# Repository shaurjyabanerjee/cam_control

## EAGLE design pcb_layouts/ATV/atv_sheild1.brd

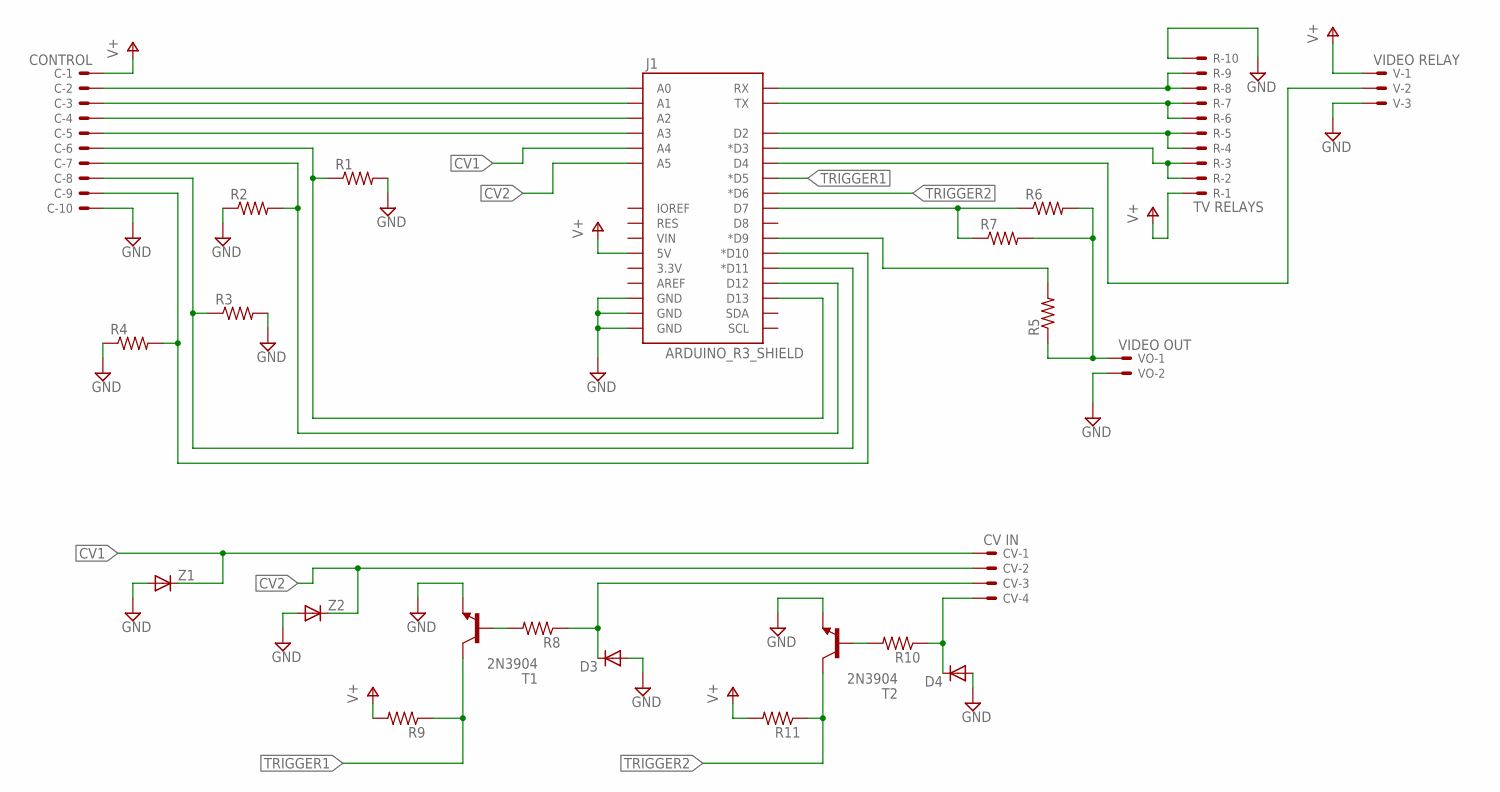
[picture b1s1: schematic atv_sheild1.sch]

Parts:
C: CONTROL; 22-23-2101
CV: CV IN; 22-23-2041
D3, D4: SMALL_DIODEDO35-7; DO35-7
J1: ARDUINO_R3_SHIELD; UNO_R3_SHIELD
R: TV RELAYS; 22-23-2101
R1, R2, R3, R4, R5, R6, R7, R8, R9, R10, R11: RESISTORPTH-1/4W; AXIAL-0.4
T1, T2: 2N3904; TO92
V: VIDEO RELAY; 22-23-2031
VO: VIDEO OUT; 22-23-2021
Z1, Z2: SMALL_DIODEDO35-7; DO35-7

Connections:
CV1: CV.1, J1.A4, Z1.C
CV2: CV.2, J1.A5, Z2.C
GND: C.10, D3.A, D4.A, J1.GND@0 (GND), J1.GND@1 (GND), J1.GND@2 (GND), R.10, R1.P$2 (2), R2.P$1 (1), R3.P$2 (2), R4.P$1 (1), T1.3 (E), T2.3 (E), V.3, VO.2, Z1.A, Z2.A
unnamed: J1.TX, R.6, R.7
unnamed: J1.D2, R.4, R.5
unnamed: J1.D3 (*D3), R.2, R.3
unnamed: J1.D4, V.2
unnamed: C.5, J1.A3
unnamed: C.2, J1.A0
unnamed: C.3, J1.A1
unnamed: C.4, J1.A2
unnamed: C.6, J1.D13, R1.P$1 (1)
unnamed: C.7, J1.D12, R2.P$2 (2)
unnamed: C.8, J1.D11 (*D11), R3.P$1 (1)
unnamed: C.9, J1.D10 (*D10), R4.P$2 (2)
unnamed: CV.3, D3.C, R8.P$1 (1)
unnamed: R5.P$1 (1), R6.P$2 (2), R7.P$2 (2), VO.1
unnamed: J1.D7, R6.P$1 (1), R7.P$1 (1)
unnamed: J1.D9 (*D9), R5.P$2 (2)
unnamed: R8.P$2 (2), T1.2 (B)
unnamed: CV.4, D4.C, R10.P$1 (1)
unnamed: J1.RX, R.8, R.9
unnamed: R10.P$2 (2), T2.2 (B)
TRIGGER1: J1.D5 (*D5), R9.P$1 (1), T1.1 (C)
TRIGGER2: J1.D6 (*D6), R11.P$1 (1), T2.1 (C)
V+: C.1, J1.5V, R.1, R9.P$2 (2), R11.P$2 (2), V.1

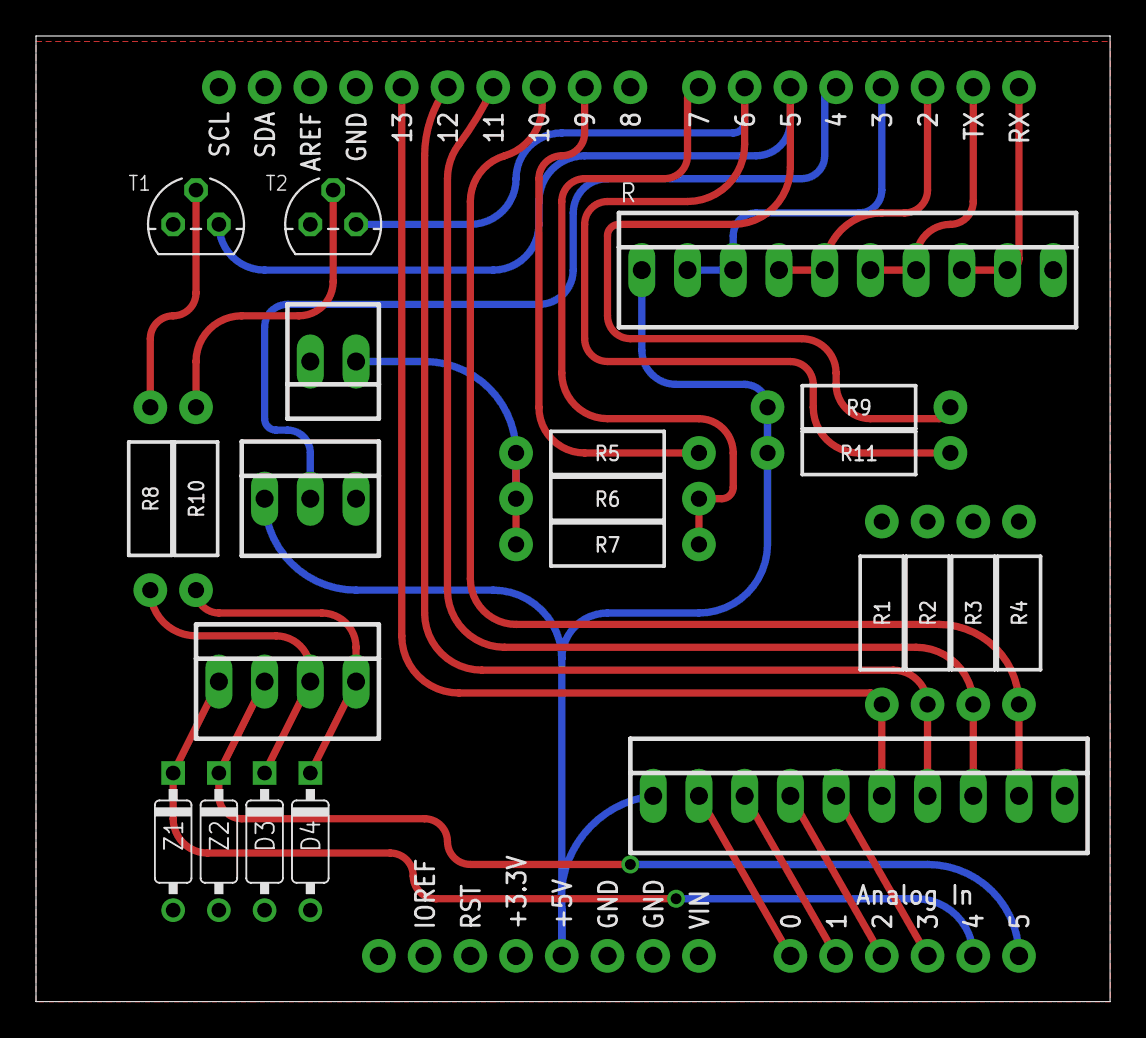
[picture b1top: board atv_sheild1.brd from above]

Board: 2 copper layers, 59.7 x 53.6 mm, 23 parts (0 on the bottom side), 26 nets.

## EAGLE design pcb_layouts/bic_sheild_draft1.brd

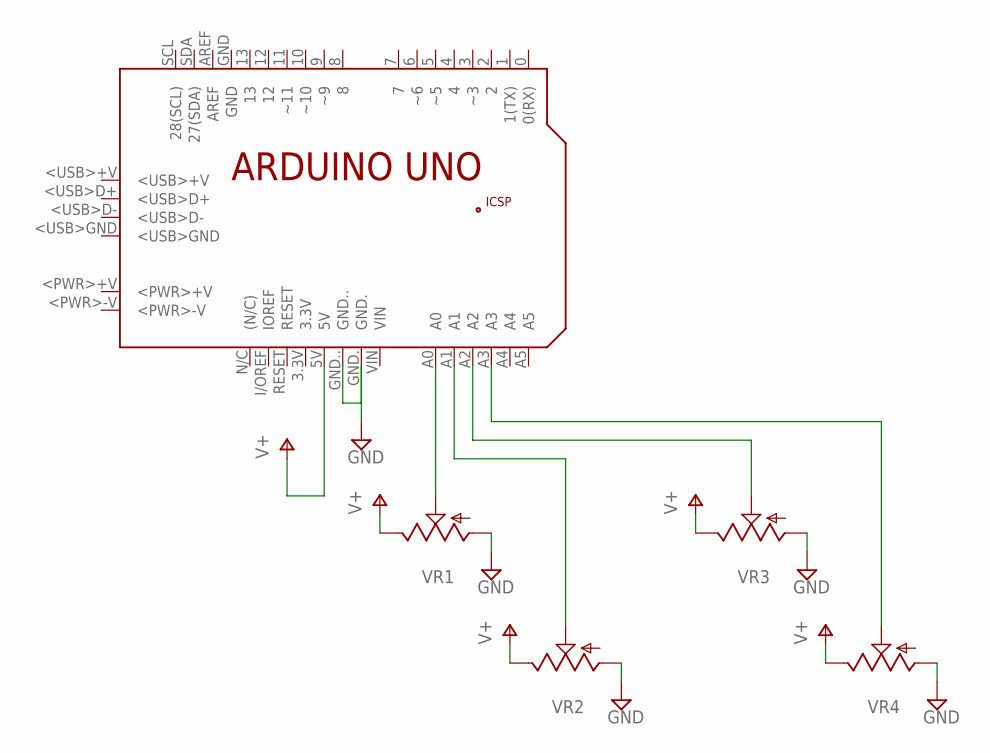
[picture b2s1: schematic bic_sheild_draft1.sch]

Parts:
PCB1: ARDUINO_UNO
VR1, VR2, VR3, VR4: 9MM_SNAP-IN_POT_; 9MM_SNAP-IN_POT

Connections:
GND: PCB1.GND., PCB1.GND.., VR1.1 (A), VR2.1 (A), VR3.1 (A), VR4.1 (A)
unnamed: PCB1.A0, VR1.2 (S)
unnamed: PCB1.A1, VR2.2 (S)
unnamed: PCB1.A2, VR3.2 (S)
unnamed: PCB1.A3, VR4.2 (S)
V+: PCB1.5V, VR1.3 (E), VR2.3 (E), VR3.3 (E), VR4.3 (E)

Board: 2 copper layers, 5 parts (0 on the bottom side), 6 nets, no tracks yet.

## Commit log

2017-12-18 updated firmware, created beaver bitmaps
2017-12-19 added shutter during manual jog feature
2017-12-23 added gfx for selectable interfocal distances
2017-12-26 fixed and noted step delay to prevent motor stalling
2017-12-26 tuned step delays, added speed control to stereo pix mode
2017-12-26 finished ALL stereo photography mode features
2017-12-27 added and tested ease ins
2017-12-29 wrote basic gfx for time lapse controller submenu
2017-12-29 added minute and hour calculations for total time
2018-01-02 tested basic intervalometer functionality, need to add viz
2018-01-02 added visualization for time lapse controller progress
2018-01-05 added and tested panning timelapse mode and GFX
2018-01-15 fixed annoying bug on interval selector
2018-01-15 added exit functionality to timelapse modes
2018-01-25 added folder for pcb layouts
2018-01-25 updated functions for new button layouts
2018-01-30 added first test of menu firmware for apvfeedbake
2018-02-01 added and tested bytebeat le firmware
2018-03-05 updated functions
2018-03-05 byteBeatEditor
2018-03-29 add bytebeatThiz
2018-04-20 remove bad things and add good things
2018-04-30 cmd-s
2018-06-11 added new keyframer draft
2018-06-12 File > New... keyframes
2018-06-12 finish use of inputDebounce library
2018-06-19 add convenient interface for long and short button presses, via InputDebounce library. preserved old button press logic for use in manual_jog function. stub keyframe logic
2018-06-19 store keyframe with long press on button 3, print list of keyframes with long press on button 1, go to keyframe with short press on button 3 (only goes to the first keyframe rn), print the motor posi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
2018-06-20 don't give negative numbers to move_step(), there is a direction parameter instead

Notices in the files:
parts and their libraries:
SparkFun-Boards: Licensing: Creative Commons ShareAlike 4.0 International - https://creativecommons.org/licenses/by-sa/4.0
